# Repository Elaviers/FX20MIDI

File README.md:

# FX20MIDI
 MIDI out for Yamaha FX-20 organ using an Arduino Due

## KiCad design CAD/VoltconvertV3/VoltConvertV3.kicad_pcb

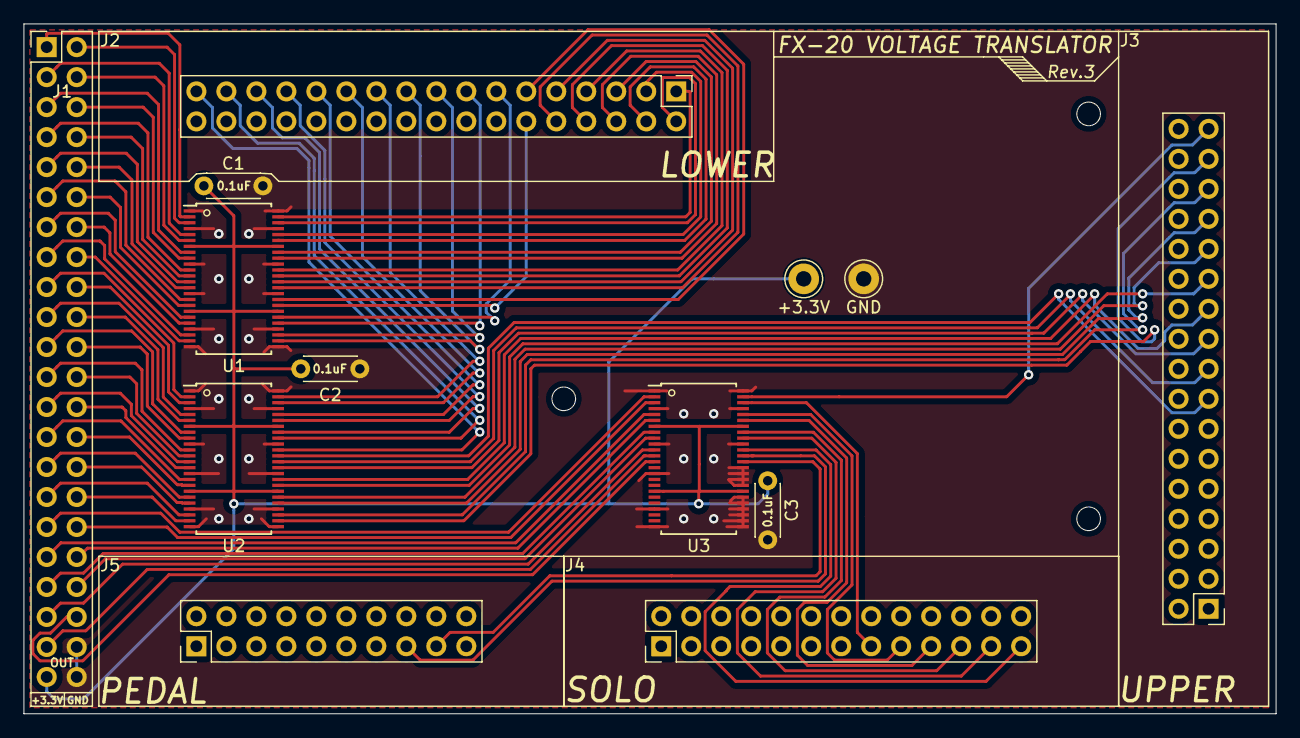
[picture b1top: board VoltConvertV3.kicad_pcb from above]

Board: 2 copper layers, 106.0 x 58.4 mm, 13 parts (0 on the bottom side), 84 nets.

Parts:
+3.3V: Pin_D1.3mm_L11.0mm
C1, C2, C3: 0.1uF; C_Disc_D4.3mm_W1.9mm_P5.00mm
GND: Pin_D1.3mm_L11.0mm
J1: OUT; PinSocket_2x22_P2.54mm_Vertical
J2: LOWER; PinHeader_2x17_P2.54mm_Vertical
J3: UPPER; PinHeader_2x17_P2.54mm_Vertical
J4: SOLO; PinHeader_2x13_P2.54mm_Vertical
J5: PEDAL; PinHeader_2x10_P2.54mm_Vertical
U1, U2, U3: 74LVC16244A; TSSOP-48_6.1x12.5mm_P0.5mm

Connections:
/+3.3V: +3.3V.1, C1.2, C2.2, C3.2, J1.43, U1.7, U1.18, U1.31, U1.42, U2.7, U2.18, U2.31, U2.42, U3.7, U3.18, U3.31, U3.42
/A: J1.10, U1.14
/AS: J1.11, U1.16
/ASi: J2.11, U1.33
/Ai: J2.10, U1.35
/B: J1.12, U1.17
/Bi: J2.12, U1.32
/C: J1.13, U1.19
/CL: J1.1, U1.2
/CLi: J2.1, U1.47
/CS: J1.2, U1.3
/CSi: J2.2, U1.46
/Ci: J2.13, U1.30
/D: J1.3, U1.5
/DS: J1.4, U1.6
/DSi: J2.4, U1.43
/Di: J2.3, U1.44
/E: J1.5, U1.8
/Ei: J2.5, U1.41
/F: J1.6, U1.9
/FS: J1.7, U1.11
/FSi: J2.7, U1.38
/Fi: J2.6, U1.40
/G: J1.8, U1.12
/GND: C1.1, C2.1, C3.1, GND.1, J1.42, J1.44, U1.1, U1.4, U1.10, U1.15, U1.21, U1.24, U1.25, U1.28, U1.34, U1.39, U1.45, U1.48, U2.1, U2.4, U2.10, U2.15, U2.21, U2.24, U2.25, U2.28, U2.34, U2.39, U2.45, U2.48, U3.1, U3.4, U3.10, U3.15, U3.21, U3.24, U3.25, U3.26, U3.27, U3.28, U3.29, U3.30, U3.32, U3.33, U3.34, U3.35, U3.39, U3.45, U3.48
/GS: J1.9, U1.13
/GSi: J2.9, U1.36
/Gi: J2.8, U1.37
/LD0: J1.19, U2.5
/LD0i: J2.25, U2.44
/LD1: J1.20, U2.6
/LD1i: J2.27, U2.43
/LD2: J1.21, U2.8
/LD2i: J2.29, U2.41
/LD3: J1.22, U2.9
/LD3i: J2.31, U2.40
/LD4: J1.23, U2.11
/LD4i: J2.33, U2.38
/LU0: J1.18, U2.3
/LU0i: J2.23, U2.46
/LU1: J1.17, U2.2
/LU1i: J2.21, U2.47
/LU2: J1.16, U1.23
/LU2i: J2.19, U1.26
/LU3: J1.15, U1.22
/LU3i: J2.17, U1.27
/LU4: J1.14, U1.20
/LU4i: J2.15, U1.29
/PD0: J1.40, U3.13
/PD0i: J5.17, U3.36
/PD1: J1.41, U3.12
/PD1i: J5.15, U3.37
/SD2: J1.37, U3.8
/SD2i: J4.21, U3.41
/SD3: J1.38, U3.9
/SD3i: J4.23, U3.40
/SD4: J1.39, U3.11
/SD4i: J4.25, U3.38
/SU2: J1.36, U3.6
/SU2i: J4.19, U3.43
/SU3: J1.35, U3.5
/SU3i: J4.17, U3.44
/SU4: J1.34, U3.3
/SU4i: J4.15, U3.46
/UD0: J1.29, U2.19
/UD0i: J3.25, U2.30
/UD1: J1.30, U2.20
/UD1i: J3.27, U2.29
/UD2: J1.31, U2.22
/UD2i: J3.29, U2.27
/UD3: J1.32, U2.23
/UD3i: J3.31, U2.26
/UD4: J1.33, U3.2
/UD4i: J3.33, U3.47
/UU0: J1.28, U2.17
/UU0i: J3.23, U2.32
/UU1: J1.27, U2.16
/UU1i: J3.21, U2.33
/UU2: J1.26, U2.14
/UU2i: J3.19, U2.35
/UU3: J1.25, U2.13
/UU3i: J3.17, U2.36
/UU4: J1.24, U2.12
/UU4i: J3.15, U2.37

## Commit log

2020-01-02 Add velocity sensing
2020-01-02 Make velocity sensing toggleable
2020-01-02 Timing Hack
    Yields (almost) perfect timing for some reason as long as you compile with O1 optimisation. :neutral_face:
2020-01-03 Cleanup
2020-01-26 NOP hack tweak
2021-08-24 Expression pedal, use asm for time-sensitive stuff, general stability improvements
